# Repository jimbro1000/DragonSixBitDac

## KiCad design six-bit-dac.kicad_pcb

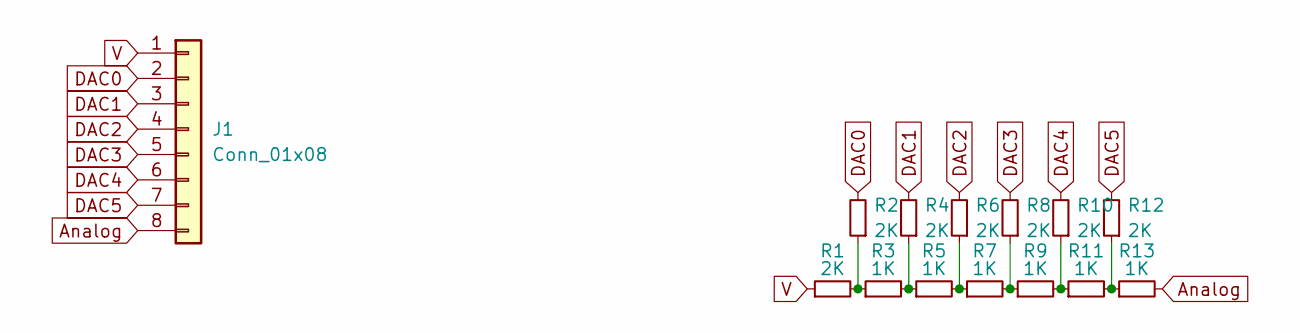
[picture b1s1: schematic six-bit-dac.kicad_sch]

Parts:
J1: Conn_01x08; PinHeader_1x08_P2.54mm_Horizontal
R1, R2, R4, R6, R8, R10, R12: 2K; R_0805_2012Metric_Pad1.20x1.40mm_HandSolder
R3, R5, R7, R9, R11, R13: 1K; R_0805_2012Metric_Pad1.20x1.40mm_HandSolder

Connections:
Analog: J1.8, R13.2
DAC0: J1.2, R2.2
DAC1: J1.3, R4.2
DAC2: J1.4, R6.2
DAC3: J1.5, R8.2
DAC4: J1.6, R10.2
DAC5: J1.7, R12.2
unnamed: R1.2, R2.1, R3.1
unnamed: R3.2, R4.1, R5.1
unnamed: R5.2, R6.1, R7.1
unnamed: R7.2, R8.1, R9.1
unnamed: R9.2, R10.1, R11.1
unnamed: R11.2, R12.1, R13.1
V: J1.1, R1.1

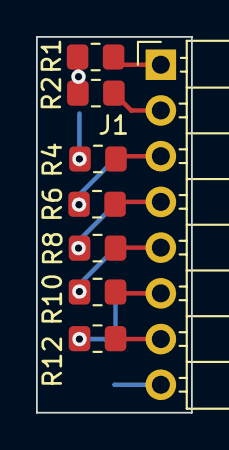
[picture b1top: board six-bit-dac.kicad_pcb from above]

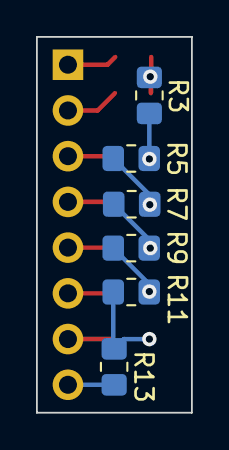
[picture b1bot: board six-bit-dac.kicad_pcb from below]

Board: 2 copper layers, 8.6 x 20.9 mm, 14 parts (6 on the bottom side), 14 nets.
